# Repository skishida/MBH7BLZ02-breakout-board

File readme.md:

View this project on [CADLAB.io](https://cadlab.io/node/920). 

# MBH7BLZ02 breakout board

This is RedBearLab BLE nano alike breakout board for fujitsu MBH7BLZ02.

* There is no relevance between this board and RedBearLab products.

## Related information

* [MBH7BLZ02 product page](http://www.fujitsu.com/jp/group/fcl/products/pdut/detail/1186515/wirelessmodule/MBH7BLZ02)

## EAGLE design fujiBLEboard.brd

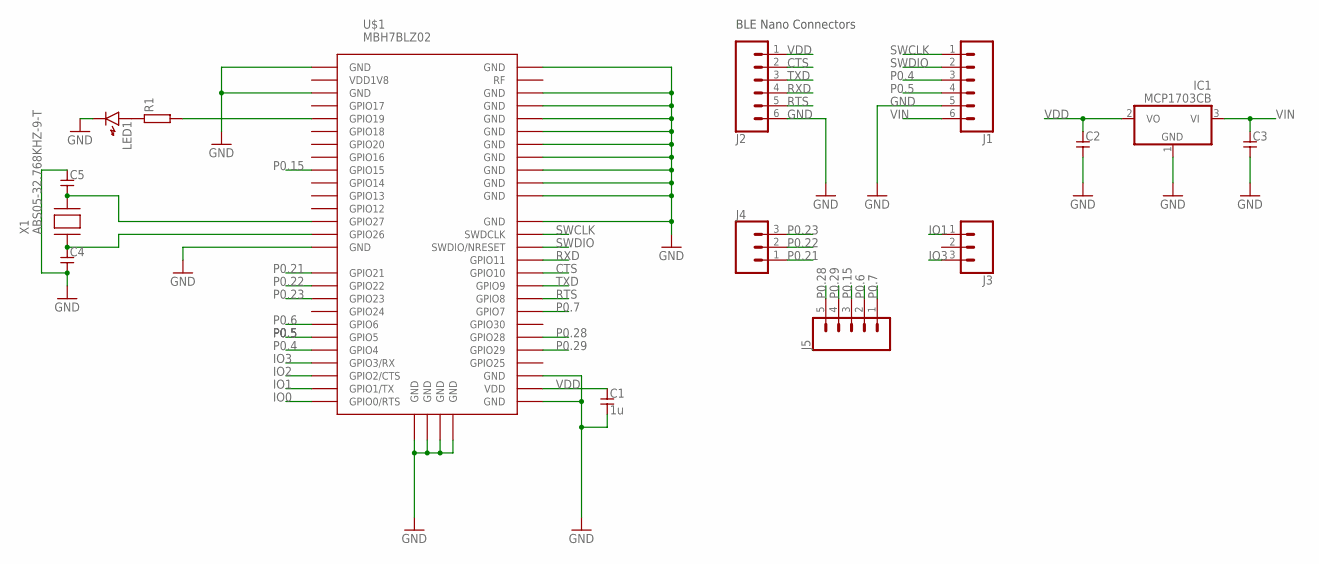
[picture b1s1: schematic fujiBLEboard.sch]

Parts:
C1: 1u; SMD1608_REDUCED
C2, C3: CAPACITOR1608_REDUCED; SMD1608_REDUCED
C4, C5: CAPACITOR1005; SMD1005
IC1: MCP1703CB; SOT23
J1, J2: CONN_06NO_SILK_FEMALE_PTH; 1X06_NO_SILK
J3, J4: CONN_031X03_NO_SILK; 1X03_NO_SILK
J5: CONN_05NO_SILK; 1X05_NO_SILK
LED1: LED1608_REDUCED
R1: RESISTOR1005; SMD1005
U$1: MBH7BLZ02
X1: ABS05-32.768KHZ-9-T; SMD1610

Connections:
CTS: J2.2, U$1.P$37 (GPIO10)
GND: C1.2, C2.2, C3.2, C4.2, C5.1, IC1.1 (GND), J1.5, J2.6, LED1.K, U$1.P$1 (GND), U$1.P$3 (GND), U$1.P$15 (GND), U$1.P$27 (GND), U$1.P$29 (GND), U$1.P$41 (GND), U$1.P$42 (GND), U$1.P$43 (GND), U$1.P$44 (GND), U$1.P$45 (GND), U$1.P$46 (GND), U$1.P$47 (GND), U$1.P$48 (GND), U$1.P$49 (GND), U$1.P$50 (GND), U$1.P$52 (GND), U$1.P$53 (GND), U$1.P$54 (GND), U$1.P$55 (GND), U$1.P$56 (GND)
IO0: U$1.P$26 (GPIO0/RTS)
IO1: J3.1, U$1.P$25 (GPIO1/TX)
IO2: U$1.P$24 (GPIO2/CTS)
IO3: J3.3, U$1.P$23 (GPIO3/RX)
unnamed: LED1.A, R1.1
unnamed: R1.2, U$1.P$5 (GPIO19)
unnamed: C4.1, U$1.P$14 (GPIO26), X1.1
unnamed: C5.2, U$1.P$13 (GPIO27), X1.2
P0.4: J1.3, U$1.P$22 (GPIO4)
P0.5: J1.4, U$1.P$21 (GPIO5)
P0.6: J5.2, U$1.P$20 (GPIO6)
P0.7: J5.1, U$1.P$34 (GPIO7)
P0.15: J5.3, U$1.P$9 (GPIO15)
P0.21: J4.1, U$1.P$16 (GPIO21)
P0.22: J4.2, U$1.P$17 (GPIO22)
P0.23: J4.3, U$1.P$18 (GPIO23)
P0.28: J5.5, U$1.P$32 (GPIO28)
P0.29: J5.4, U$1.P$31 (GPIO29)
RTS: J2.5, U$1.P$35 (GPIO8)
RXD: J2.4, U$1.P$38 (GPIO11)
SWCLK: J1.1, U$1.P$40 (SWDCLK)
SWDIO: J1.2, U$1.P$39 (SWDIO/NRESET)
TXD: J2.3, U$1.P$36 (GPIO9)
VDD: C1.1, C2.1, IC1.2 (VO), J2.1, U$1.P$28 (VDD)
VIN: C3.1, IC1.3 (VI), J1.6

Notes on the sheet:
BLE Nano Connectors

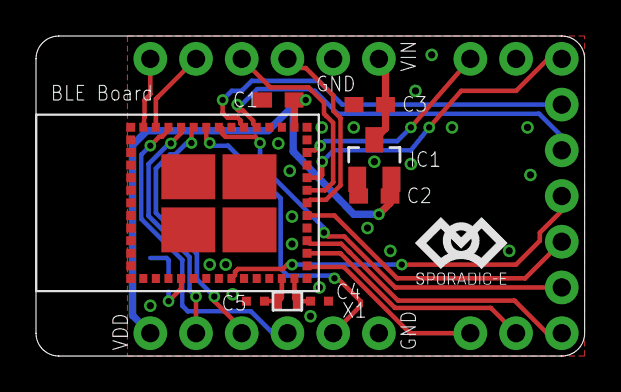
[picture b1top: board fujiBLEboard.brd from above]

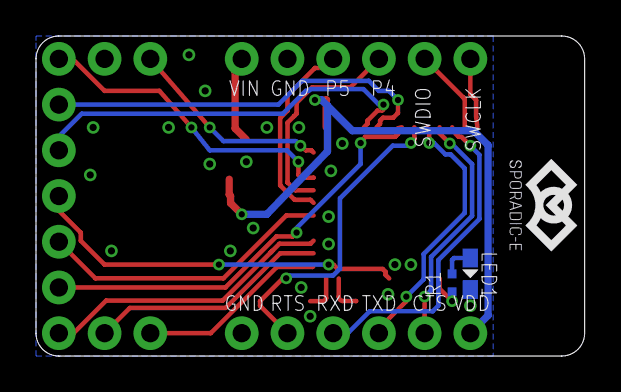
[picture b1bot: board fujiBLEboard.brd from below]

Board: 2 copper layers, 30.5 x 17.8 mm, 17 parts (3 on the bottom side), 25 nets.

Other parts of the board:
U$2, U$3: LOGO-20MM

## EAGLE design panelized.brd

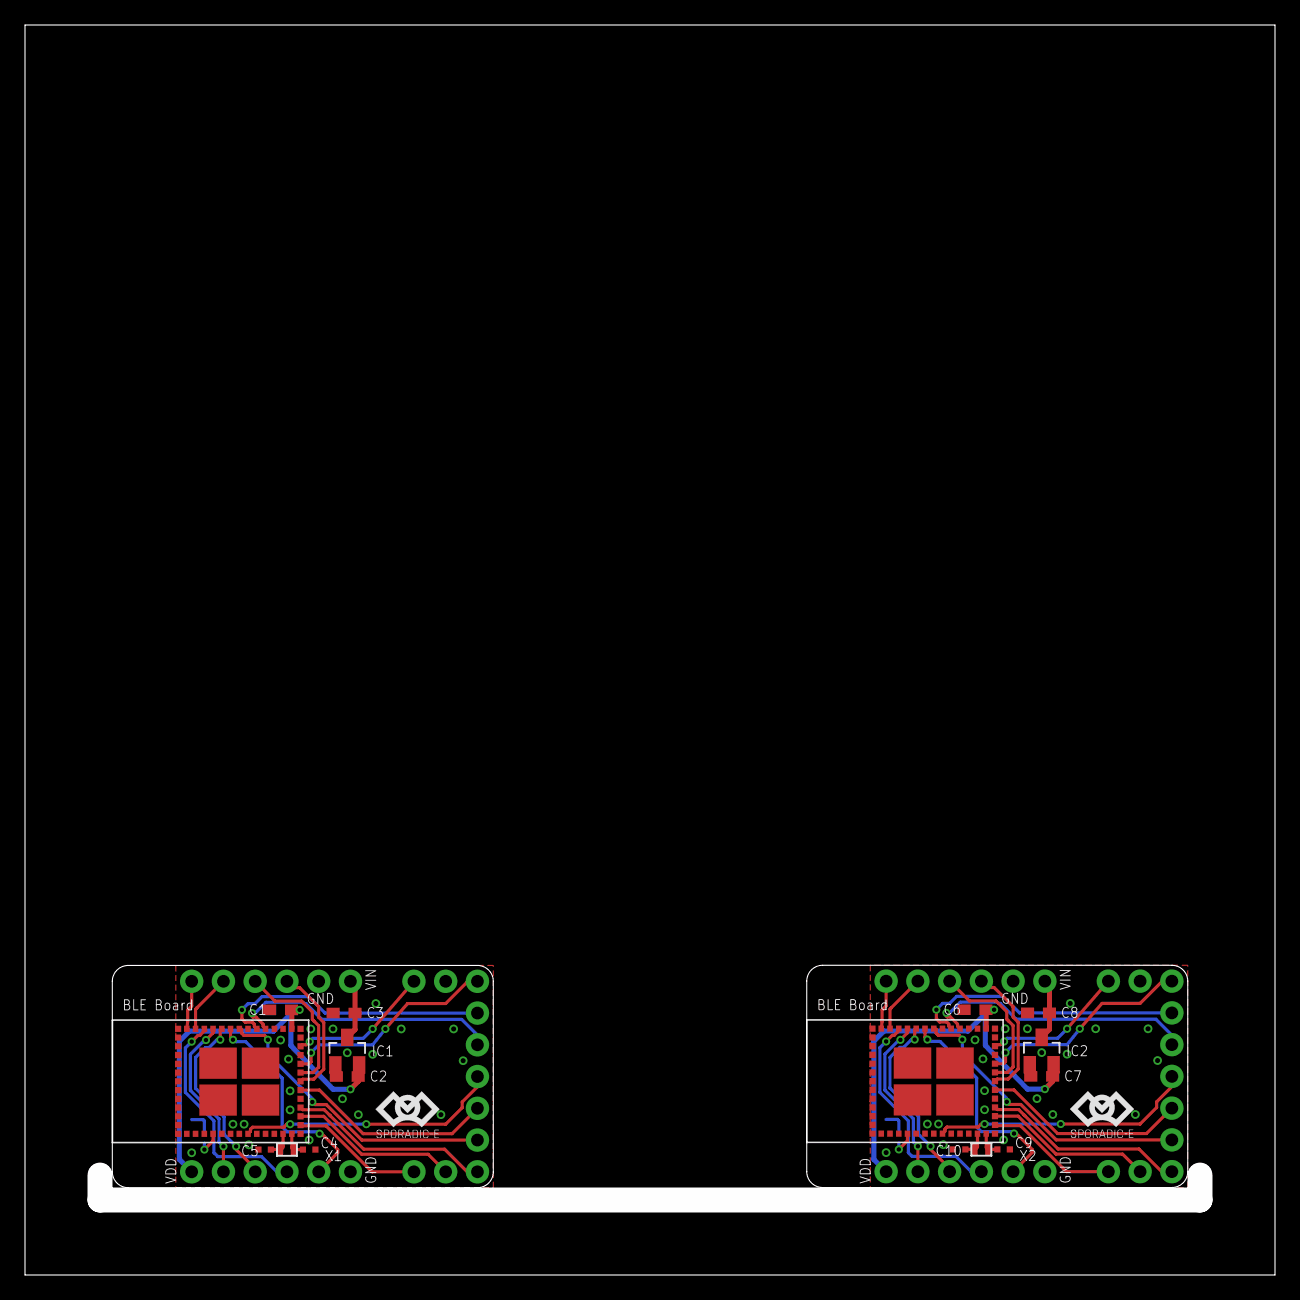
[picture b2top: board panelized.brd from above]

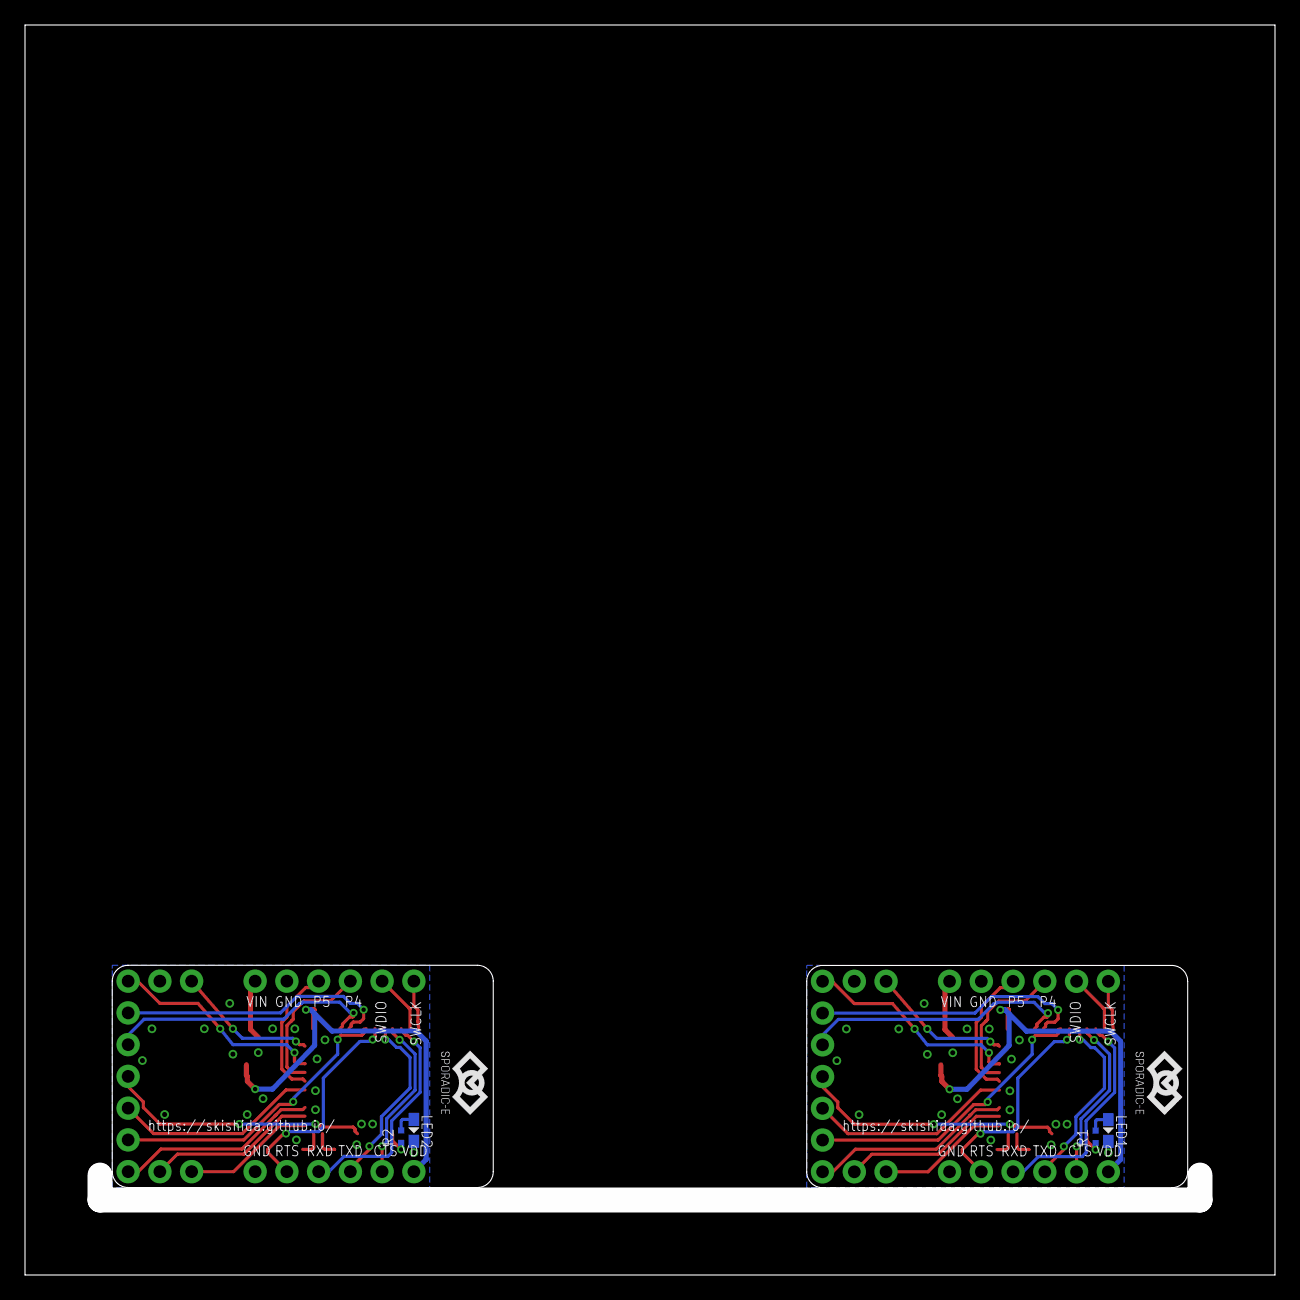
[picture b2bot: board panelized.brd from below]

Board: 2 copper layers, 100.0 x 100.0 mm, 34 parts (6 on the bottom side), 50 nets.

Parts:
C1, C6: 1u; SMD1608_REDUCED
C2, C3, C7, C8: SMD1608_REDUCED
C4, C5, C9, C10: SMD1005
IC1, IC2: MCP1703CB; SOT23
J1, J2, J6, J7: 1X06_NO_SILK
J3, J4, J8, J9: 1X03_NO_SILK
J5, J10: 1X05_NO_SILK
LED1, LED2: LED1608_REDUCED
R1, R2: SMD1005
U$1, U$4: MBH7BLZ02
U$2, U$3, U$5, U$6: LOGO-20MM
X1, X2: ABS05-32.768KHZ-9-T; SMD1610

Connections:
CTS: J2.2, U$1.P$37
CTS1: J7.2, U$4.P$37
GND: C1.2, C2.2, C3.2, C4.2, C5.1, IC1.1, J1.5, J2.6, LED1.K, U$1.P$1, U$1.P$3, U$1.P$15, U$1.P$27, U$1.P$29, U$1.P$41, U$1.P$42, U$1.P$43, U$1.P$44, U$1.P$45, U$1.P$46, U$1.P$47, U$1.P$48, U$1.P$49, U$1.P$50, U$1.P$52, U$1.P$53, U$1.P$54, U$1.P$55, U$1.P$56
GND1: C6.2, C7.2, C8.2, C9.2, C10.1, IC2.1, J6.5, J7.6, LED2.K, U$4.P$1, U$4.P$3, U$4.P$15, U$4.P$27, U$4.P$29, U$4.P$41, U$4.P$42, U$4.P$43, U$4.P$44, U$4.P$45, U$4.P$46, U$4.P$47, U$4.P$48, U$4.P$49, U$4.P$50, U$4.P$52, U$4.P$53, U$4.P$54, U$4.P$55, U$4.P$56
IO1: J3.1, U$1.P$25
IO3: J3.3, U$1.P$23
IO5: J8.1, U$4.P$25
IO7: J8.3, U$4.P$23
unnamed: LED1.A, R1.1
unnamed: R1.2, U$1.P$5
unnamed: C9.1, U$4.P$14, X2.1
unnamed: C10.2, U$4.P$13, X2.2
unnamed: LED2.A, R2.1
unnamed: C4.1, U$1.P$14, X1.1
unnamed: C5.2, U$1.P$13, X1.2
unnamed: R2.2, U$4.P$5
P0.1: J6.3, U$4.P$22
P0.2: J6.4, U$4.P$21
P0.3: J10.1, U$4.P$34
P0.4: J1.3, U$1.P$22
P0.5: J1.4, U$1.P$21
P0.6: J5.2, U$1.P$20
P0.7: J5.1, U$1.P$34
P0.8: J10.2, U$4.P$20
P0.9: J10.3, U$4.P$9
P0.10: J10.4, U$4.P$31
P0.11: J10.5, U$4.P$32
P0.12: J9.1, U$4.P$16
P0.13: J9.2, U$4.P$17
P0.14: J9.3, U$4.P$18
P0.15: J5.3, U$1.P$9
P0.21: J4.1, U$1.P$16
P0.22: J4.2, U$1.P$17
P0.23: J4.3, U$1.P$18
P0.28: J5.5, U$1.P$32
P0.29: J5.4, U$1.P$31
RTS: J2.5, U$1.P$35
RTS1: J7.5, U$4.P$35
RXD: J2.4, U$1.P$38
RXD1: J7.4, U$4.P$38
SWCLK: J1.1, U$1.P$40
SWCLK1: J6.1, U$4.P$40
SWDIO: J1.2, U$1.P$39
SWDIO1: J6.2, U$4.P$39
TXD: J2.3, U$1.P$36
TXD1: J7.3, U$4.P$36
VDD: C1.1, C2.1, IC1.2, J2.1, U$1.P$28
VDD1: C6.1, C7.1, IC2.2, J7.1, U$4.P$28
VIN: C3.1, IC1.3, J1.6
VIN1: C8.1, IC2.3, J6.6

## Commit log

2018-04-21 update gitignore
2018-04-21 add boards
2018-04-21 Create LICENSE
2018-04-23 Backlink to CADLAB.io has been added.
2018-04-23 some improvement
2018-06-05 pin mirrored

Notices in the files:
parts and their libraries:
SparkFun-Connectors: Licensing: Creative Commons ShareAlike 4.0 International - https://creativecommons.org/licenses/by-sa/4.0
